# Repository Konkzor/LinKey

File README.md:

Moniteur **open-hardware** basse consommation à base d'ESP32 pour le compteur électrique **Linky** (monophasé), avec intégration native à **Home Assistant** via MQTT.

LinKey (jeu de mot) lit la sortie série TIC (Télé-Information Client) d'un Linky monophasé et publie les mesures de puissance, d'énergie et de courant vers le broker MQTT de votre Home Assistant. Le coprocesseur ULP de l'ESP32 décode la trame TIC pendant que le CPU principal reste en *light sleep*, ce qui maintient une consommation moyenne suffisamment faible pour fonctionner sur l'alimentation de la TIC via une supercapa.

## Fonctionnalités

- Décodage UART 7E1 (1200 bauds) par le coprocesseur ULP de l'ESP32
- Boucle principale en *light sleep* avec *modem sleep* WiFi
- Publication MQTT en QoS 1, *Last Will and Testament* et auto-découverte Home Assistant
- Alimentation par supercapa avec surveillance de tension intégrée
- Retour visuel par LED RGB
- Compatible contrats BASE, HP/HC, Tempo et EJP
- Mode TIC historique (standard à venir)

## Structure du dépôt

```
.
├── CAO/        Boîtier imprimable 3D (source STEP + modèle Onshape)
├── Doc/        Spécification TIC Linky et documents de référence
├── Firmware/   Projet ESP-IDF (ULP + machine d'état CPU, WiFi/MQTT)
└── PCB/        Projet KiCad, schéma, Gerbers

```

## Documentation

- [Guide du firmware](Firmware/README.md) — compilation, flashage, configuration, topics MQTT, découverte HA
- [Guide de la carte (PCB)](PCB/README.md) — composants, brochage ESP32, connexion TIC, fabrication
- [Guide du boîtier (CAO)](CAO/README.md) — source Onshape, STEP, paramètres d'impression
- [Spécification TIC Linky](Doc/Enedis-MOP-CPT_002E.pdf) — document de référence Enedis

## Firmware

Le firmware est un projet ESP-IDF situé dans [`Firmware/`](Firmware/). Consultez [`Firmware/README.md`](Firmware/README.md) pour le guide complet de compilation, flashage et configuration.

Démarrage rapide :

```bash
git clone --recurse-submodules https://github.com/Konkzor/LinKey.git
cd LinKey/Firmware
source ~/esp/v5.4.1/esp-idf/export.sh
idf.py menuconfig    # Configurer l'appareil et les options MQTT
idf.py -p /dev/ttyUSB0 flash monitor
```

Les identifiants WiFi sont provisionnés ensuite en BLE via l'application Espressif. Le firmware tente de découvrir Home Assistant en mDNS pour construire automatiquement l'URI MQTT (`mqtt://<ha-ip>:1883`), puis utilise `mqtt://homeassistant.local:1883` comme solution de repli.

L'identité MQTT par défaut est dérivée de l'adresse MAC WiFi : utilisateur `linkey_<suffixe_mac>` et topics `linkey/<suffixe_mac>/...`, par exemple `linkey/8ebde0/state`.

## PCB

Le PCB a été réalisé sous KiCad 9.

Les sources de la carte se trouvent dans [`PCB/`](PCB/). Voir [`PCB/README.md`](PCB/README.md) pour une description des composants, le brochage de l'ESP32 et la connexion TIC.

- Projet KiCad : [`PCB/LinKey.kicad_pro`](PCB/LinKey.kicad_pro)
- Modèles 3D de certains composants : [`PCB/MCAD files/`](PCB/MCAD%20files/)

> Note : Les fichiers de fabrication et la nomenclature ne sont pas versionnés dans le repo. Ils sont disponibles en artefacts des jobs de la CI ainsi que dans la [page Releases](https://github.com/Konkzor/LinKey/releases) pour les versions taguées.

## CAO

Le boîtier est conçu sous Onshape et imprimable en 3D.

Les sources se trouvent dans [`CAO/`](CAO/). Voir [`CAO/README.md`](CAO/README.md) pour le lien vers le modèle Onshape et les paramètres d'impression conseillés.

- Source CAO neutre (STEP) ;
- Fichiers prêts à imprimer (3MF multicolore, STL mono-couleur) : [page Releases](https://github.com/Konkzor/LinKey/releases).

## Licence

Ce projet utilise une **double licence** selon la nature des fichiers :

### Matériel — CERN-OHL-W-2.0

Le matériel (`PCB/` : sources KiCad, Gerbers… et `CAO/` : modèles 3D du boîtier, pièces mécaniques) est distribué sous **CERN Open Hardware Licence Version 2 – Weakly Reciprocal (CERN-OHL-W-2.0)**.

Vous êtes libre d'utiliser, d'étudier, de modifier et de fabriquer ce matériel.
Si vous modifiez les fichiers de conception eux-mêmes, vous devez publier ces modifications sous la même licence.
En revanche, vous n'êtes pas tenu de publier les sources de produits plus larges qui ne font qu'incorporer cette conception.

Texte complet : [`LICENSE`](LICENSE) (EN).

### Firmware — MIT

Le code du firmware (`Firmware/main/`) est distribué sous **licence MIT**, plus permissive et adaptée au logiciel.

Texte complet : [`Firmware/LICENSE`](Firmware/LICENSE) (EN).

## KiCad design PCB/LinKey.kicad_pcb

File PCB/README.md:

# LinKey — Carte électronique

Sources matérielles de la carte LinKey : projet KiCad, Gerbers et nomenclature.

> [!NOTE]
> La révision PCB est portée par les **tags git** `pcb-v*` (ex. `pcb-v1.0`). C'est la **source unique** : la CI dérive la version d'`git describe --tags --match 'pcb-v*'` et l'injecte à la fois dans le nom de l'artefact (`LinKey-pcb-<version>-fab`) et dans la variable de projet `PCB_VERSION` (Board Setup → Text Variables) pour que la sérigraphie `${PCB_VERSION}` reflète exactement l'état du dépôt :
>
> | Build | `${PCB_VERSION}` et nom d'artefact |
> |-------|------------------------------------|
> | Local (export manuel depuis KiCad) | `UNCONTROLLED` — valeur fixée en dur dans [`LinKey.kicad_pro`](LinKey.kicad_pro), signale que les fichiers de fab n'ont pas été produits par la CI et ne doivent pas être utilisés |
> | CI hors tag | `vX.Y-N-gSHA` (tag le plus récent + commits depuis + hash court) |
> | CI sur un tag `pcb-vX.Y` | `vX.Y` |

## Couche physique de la TIC Linky

> Source : [Enedis-NOI-CPT_54E](../Doc/Enedis-MOP-CPT_002E.pdf), §5.3.1 *Caractéristiques des signaux* (Table 3).

La sortie TIC du compteur Linky se présente sur le bornier client sous forme de **trois bornes** (`I1`, `I2`, `A`) : la paire `I1`/`I2` véhicule les **données**, et la paire `I1`/`A` est dédiée à l'**alimentation parasite** des récepteurs. Le compteur émet sur ce bus un **signal binaire modulé par tout-ou-rien sur une porteuse 50 kHz ± 3 %** (Table 3 de la spec Enedis), avec une **logique de codage négative** (porteuse présente ⇒ « 0 », porteuse absente ⇒ « 1 ») et une transmission **unidirectionnelle**.

> [!WARNING]
> Bien que les niveaux soient bas, le bus TIC reste relié au compteur — une **isolation galvanique côté récepteur reste obligatoire** pour la sécurité utilisateur et la conformité. C'est le rôle de l'optocoupleur (voir l'étage d'entrée ci-dessous).

Le bus est connecté à la carte via le connecteur **`J1`** (Samtec **HPM-03-04-T-S**, header 3 broches, pas 5 mm, sortie à angle droit).

## Architecture du PCB

L'architecture du PCB est composée de 2 branches principales :

```mermaid
flowchart LR
    TIC([TIC Linky J1<br/>I1, I2, A])

    TIC -->|I1 / A| D1[Pont redresseur<br/>D1]
    D1 --> Charge[Circuit de charge<br/>Q1, Q2, U4]
    Charge --> C2[(C2 — 1 F<br/>supercapa)]
    C2 --> Boost[Boost 3,3 V<br/>U5 — TPS61022]
    Boost --> ESP[ESP32 WROOM-32E<br/>+ périphériques]

    TIC -->|I1 / I2| U1[Opto AC/DC<br/>U1 — ACPL-214]
    U1 -->|RX — GPIO 14| ESP

    C2 -.->|ADC GPIO 33 — V_cap| ESP
```

- **Branche supérieure** : chemin d'alimentation, sur les bornes **`I1` / `A`** du Linky → pont redresseur → circuit de charge supercapa → `C2` → boost 3,3 V → ESP32.
- **Branche inférieure** : chemin de données, sur les bornes **`I1` / `I2`** du Linky → optocoupleur → ESP32.

Remarque : En **trait pointillé** la mesure de la tension du supercondensateur par l'ESP32.

### 1. Étage d'entrée

Sépare et conditionne les deux fonctions du bus TIC.

- **Démodulation des données** — `U1` (Broadcom **ACPL-214-500E**, opto **AC** SOP-4) extrait directement l'enveloppe de la porteuse 50 kHz et fournit un signal UART démodulé côté ESP32 (pull_up `R5` incluse), tout en assurant l'isolation galvanique.
- **Pont redresseur d'alimentation** — `D1` (Infineon **BAS 4002A RPP E6327**, array de Schottky basse Vf) forme un pont à quatre diodes dans un seul boîtier qui rectifie la porteuse 50 kHz pour alimenter le reste de la carte.

### 2. Circuit de charge du supercondensateur

Stocke l'énergie disponible pour absorber les pics de consommation pendant l'émission WiFi/MQTT. Limite le courant et la tension de charge.

- **Supercondensateur** — `C2` (KYOCERA AVX **SCCR12E105SRB**, 1 F / 3 V, ESR faible, radial 8×12 mm).
- Limitation de courant et tension contrôlant la tension Vgs de `Q2` (TI **CSD25402Q3A**, P-MOSFET 20 V) :
  - **Limitation de courant** — `Q1` (ON Semi **MMBT2907A**, PNP 60 V / 0,6 A) conjugué à `R10` (10 Ω) qui fixe le seuil de courant débité par l'étage d'entrée vers la supercapa à environ  40 mA.
  - **Limitation de tension** — `U4` (TI **TL431**, référence shunt ajustable) clampe la tension de charge à 2,7V de la supercapa (seuil réglé par `R15` et `R16`).

### 3. Alimentation 3,3 V (boost)

Convertit la tension variable du supercondensateur (0 V → 2,7 V) en un rail 3,3 V stable pour l'ESP32.

- **Convertisseur** — `U5` (TI **TPS61022**, boost synchrone 8 A pic, **démarrage à 1,5 V, maintien jusqu'à 0,5 V**) : on peut tirer du jus de la supercapa presque jusqu'à le vider complètement.
- **Inductance** — `L1` (Coilcraft **XEL5030-102MEC**, 1 µH), recommandée par TI.
- **Capacités** — `C3`, `C4` pour l'entrée, `C6` (22 µF / 10 V X7R 1206) pour la sortie.
- **Pont diviseur** — `R17` (453 k) / `R18` (100 k) pour régler la sortie à 3,3 V.

### 4. ESP32 et périphériques

- **MCU** — `U2` (Espressif **ESP32-WROOM-32E-N8**, 8 MB flash SPI, antenne PCB intégrée). Module choisi pour sa disponibilité du **coprocesseur ULP** que le firmware utilise pour décoder la TIC pendant le *light sleep*.
- **Découplage** — `C8` (100 nF), `C7` (22 µF).
- **Interface programmation/debug** — `J2` (header 4 broches, pas 2,54 mm) expose `TX`, `RX`, `GND`, `3V3` pour le flashage et le debug.
- **Boutons** — deux boutons tactiles Omron **B3U-1000P** :
  - `SW1` — **RESET**, raccordé sur la broche `EN` de l'ESP32 (tient le module en reset tant qu'il est pressé).
  - `SW2` — **BOOT**, raccordé sur `IO0` ; à maintenir pendant un reset pour entrer en mode flashage.
- **LED d'état RGB** — `D8` (American Bright **BL-HBXJXGX32L**, 5050 PLCC6) avec ses résistances de limitation `R6` (120 Ω) / `R8` (330 Ω) / `R9` (120 Ω) sur les trois canaux B/R/G respectivement. Pilotée par GPIO 2 / 13 / 15 ; flash bref de 10 ms à chaque itération de la FSM (voir `Firmware/README.md`).

## Affectation des broches (ESP32)

| Fonction | GPIO |
|----------|------|
| RX TIC Linky | 14 |
| ADC tension supercondensateur | 33 |
| LED RGB Rouge | 13 |
| LED RGB Verte | 15 |
| LED RGB Bleue | 2 |
| RX UART ESP | 3 |
| TX UART ESP | 1 |

## Contenu du dossier

| Fichier / dossier | Description |
|-------------------|-------------|
| [`LinKey.kicad_pro`](LinKey.kicad_pro) | Projet KiCad 9 |
| [`LinKey.kicad_sch`](LinKey.kicad_sch) | Schéma |
| [`LinKey.kicad_pcb`](LinKey.kicad_pcb) | Routage |
| [`fab-output.kicad_jobset`](fab-output.kicad_jobset) | Jobset KiCad décrivant les sorties de fabrication générées en CI |
| [`MCAD files/`](MCAD%20files/) | Modèles 3D des composants (STEP) |
| [`LinKey_Lib_Footprints.pretty/`](LinKey_Lib_Footprints.pretty/) | Bibliothèque d'empreintes du projet |
| [`LinKey_Lib_Symbols.kicad_sym`](LinKey_Lib_Symbols.kicad_sym) | Bibliothèque de symboles du projet |

## Fabrication

Les fichiers de fabrication ne sont **pas versionnés** : ils sont régénérés à chaque push par le workflow GitHub Actions [`.github/workflows/ci.yml`](../.github/workflows/ci.yml) (job `pcb-fab`) à partir du jobset [`fab-output.kicad_jobset`](fab-output.kicad_jobset), et publiés en tant qu'artefact nommé **`LinKey-pcb-<PCB_VERSION>-fab`** sur l'exécution correspondante (la version provient de la variable de projet `PCB_VERSION` — cf. note en haut de ce README).

Contenu de l'artefact :

| Fichier | Description |
|---------|-------------|
| `gerbers/LinKey-F_Cu.gbr`, `B_Cu.gbr`, `In1_Cu.gbr`, `In2_Cu.gbr` | Couches cuivre (4 couches) |
| `gerbers/LinKey-F_Mask.gbr`, `B_Mask.gbr` | Masques de soudure |
| `gerbers/LinKey-F_Paste.gbr`, `B_Paste.gbr` | Pochoir pâte à braser |
| `gerbers/LinKey-F_Silkscreen.gbr`, `B_Silkscreen.gbr` | Sérigraphies |
| `gerbers/LinKey-Edge_Cuts.gbr` | Contour de la carte |
| `gerbers/LinKey-job.gbrjob` | Métadonnées Gerber X2 (stackup) |
| `LinKey-PTH.drl`, `LinKey-NPTH.drl` | Perçages (plaqués / non plaqués) |
| `LinKey_positions-all.csv` | Fichier de positions (pick & place) |
| `LinKey_Bill_of_Materials.csv` | Nomenclature (BOM) |

Pour récupérer l'archive : ouvrir l'exécution CI sur GitHub → onglet *Summary* → section *Artifacts* → **`LinKey-pcb-<PCB_VERSION>-fab`**.

## Consommation

- ***Light sleep*** : à mesurer
- **Actif (publication)** : à mesurer
- **Moyenne** : à mesurer

## Licence

Voir le fichier [LICENSE](../LICENSE) à la racine du dépôt (CERN-OHL-W-2.0).

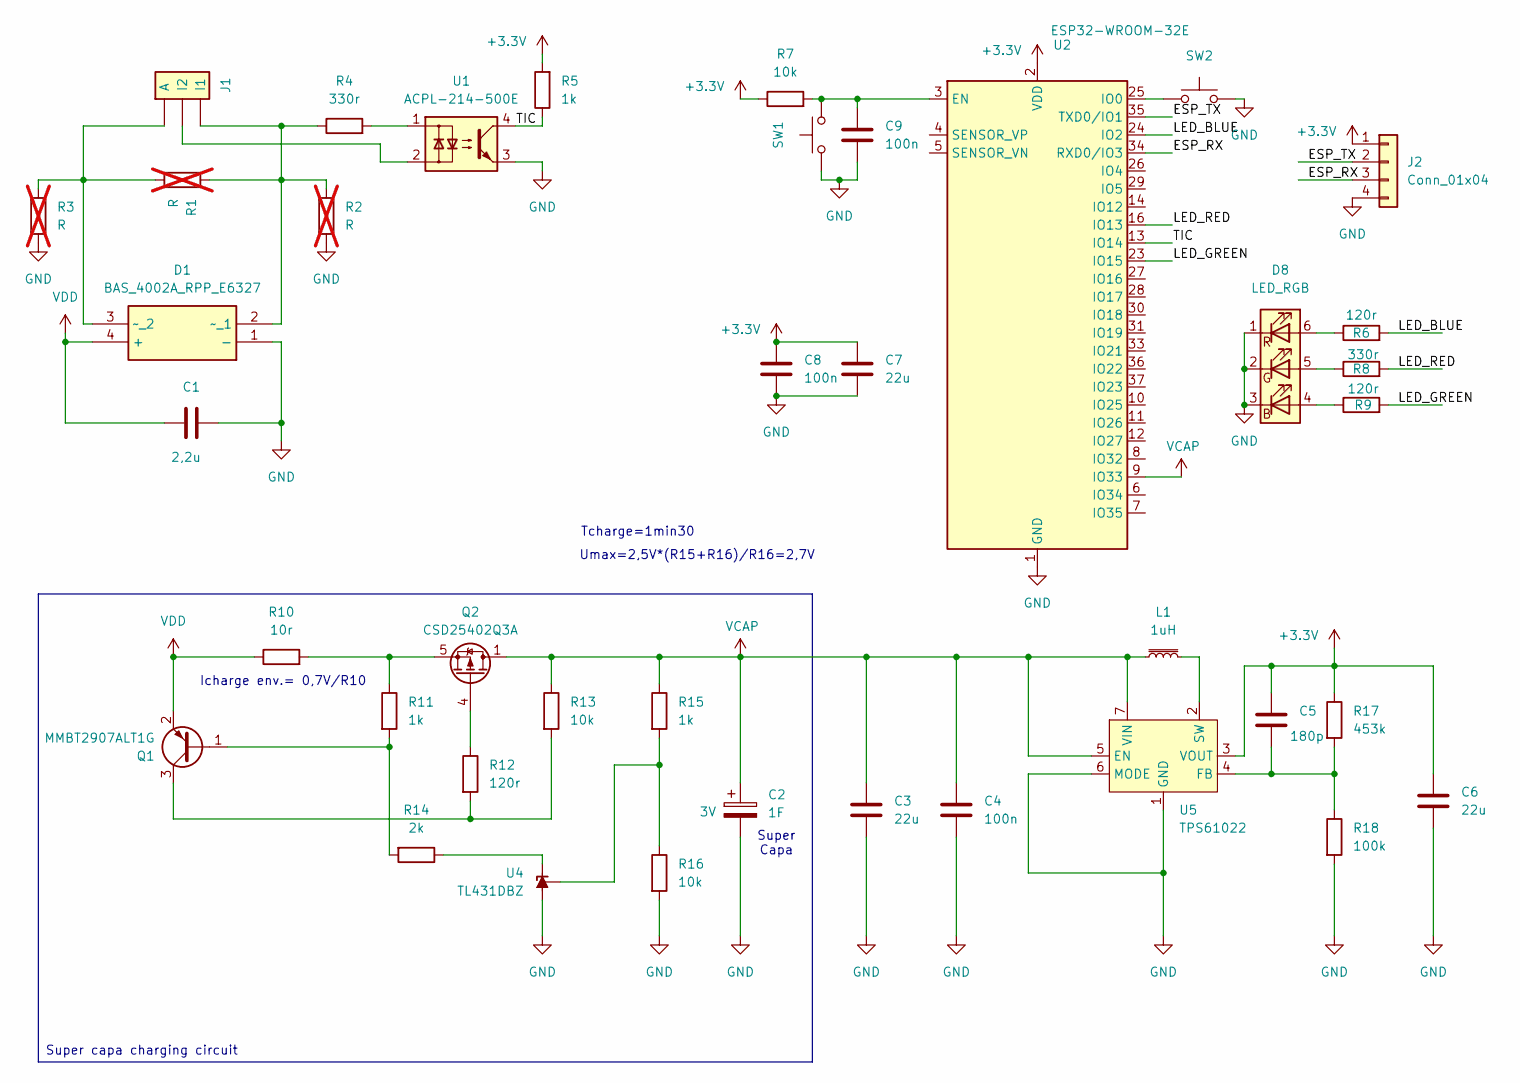
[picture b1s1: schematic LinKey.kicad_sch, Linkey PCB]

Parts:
C1: 2,2u; C_0805_2012Metric_Pad1.18x1.45mm_HandSolder; Voltage 16V; Manufacturer_Part_Number CL21B225KOFNNNF
C2: 1F; CP_Radial_D8.0mm_P3.50mm; Voltage 3V; Manufacturer_Part_Number SCCR12E105SRB
C3, C6, C7: 22u; C_1206_3216Metric_Pad1.33x1.80mm_HandSolder; Voltage 10V; Manufacturer_Part_Number CL31B226KPHNNNE
C4, C8, C9: 100n; C_0603_1608Metric_Pad1.08x0.95mm_HandSolder; Voltage 50V; Manufacturer_Part_Number CC0603JRX7R9BB104
C5: 180p; C_0603_1608Metric_Pad1.08x0.95mm_HandSolder; Voltage 50V; Manufacturer_Part_Number CC603KRX7R9BB181
D1: BAS_4002A_RPP_E6327; BAS4002ARPPE6327; Manufacturer_Part_Number BAS 4002A RPP E6327
D8: LED_RGB; LED_RGB_5050-6; Manufacturer_Part_Number BL-HBXJXGX32L
J1: Conn_01x03_TIC; Manufacturer_Part_Number HPM-03-04-T-S
J2: Conn_01x04; PinHeader_1x04_P2.54mm_Vertical
L1: 1uH; L_Coilcraft_XAL5030-XXX; Manufacturer_Part_Number XEL5030-102MEC
Q1: MMBT2907ALT1G; SOT-23_Handsoldering; Voltage 60V; Manufacturer_Part_Number MMBT2907ALT1G
Q2: CSD25402Q3A; VSON-8_3.3x3.3mm_P0.65mm_NexFET; Voltage 20V; Manufacturer_Part_Number CSD25402Q3A
R1, R2, R3: R; R_0603_1608Metric_Pad0.98x0.95mm_HandSolder; not fitted
R4, R8: 330r; R_0603_1608Metric_Pad0.98x0.95mm_HandSolder; Voltage 75V; Manufacturer_Part_Number CRCW0603330RFKEAC
R5, R11, R15: 1k; R_0603_1608Metric_Pad0.98x0.95mm_HandSolder; Voltage 75V; Manufacturer_Part_Number CRCW06031K00FKEAC
R6, R9, R12: 120r; R_0603_1608Metric_Pad0.98x0.95mm_HandSolder; Voltage 75V; Manufacturer_Part_Number CRCW0603120RFKEAC
R7, R13, R16: 10k; R_0603_1608Metric_Pad0.98x0.95mm_HandSolder; Voltage 75V; Manufacturer_Part_Number CRCW060310K0FKECC
R10: 10r; R_0805_2012Metric_Pad1.20x1.40mm_HandSolder; Voltage 150V; Manufacturer_Part_Number CRCW080510R0FKEA
R14: 2k; R_0603_1608Metric_Pad0.98x0.95mm_HandSolder; Voltage 75V; Manufacturer_Part_Number CRCW06032K00FKEAC
R17: 453k; R_0603_1608Metric_Pad0.98x0.95mm_HandSolder; Manufacturer_Part_Number CRCW0603453KFKEAC
R18: 100k; R_0603_1608Metric_Pad0.98x0.95mm_HandSolder; Voltage 75V; Manufacturer_Part_Number CRCW0603100KFKEAC
SW1, SW2: B3U-1000P; Manufacturer_Part_Number B3U-1000P
U1: ACPL-214-500E; SOP-4_4.4x2.6mm_P1.27mm; Manufacturer_Part_Number ACPL-214-500E
U2: ESP32-WROOM-32E; Manufacturer_Part_Number ESP32-WROOM-32E-N8
U4: TL431DBZ; SOT-23; Manufacturer_Part_Number TL431AIDBZR
U5: TPS61022; Texas_RWU0007A_VQFN-7_2x2mm_P0.5mm; Manufacturer_Part_Number TPS61022RWUT

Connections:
+3.3V: C5.1, C6.1, C7.1, C8.1, J2.1, R5.2, R7.1, R17.1, U2.2 (VDD), U5.3 (VOUT)
/ESP_RX: J2.3, U2.34 (RXD0/IO3)
/ESP_TX: J2.2, U2.35 (TXD0/IO1)
/LED_BLUE: R6.2, U2.24 (IO2)
/LED_GREEN: R9.2, U2.23 (IO15)
/LED_RED: R8.2, U2.16 (IO13)
/TIC: R5.1, U1.4, U2.13 (IO14)
GND: C1.2, C2.2, C3.2, C4.2, C6.2, C7.2, C8.2, C9.2, D1.1 (-), D8.1 (RK), D8.2 (GK), D8.3 (BK), J2.4, R2.2, R3.2, R16.2, R18.2, SW1.1, SW2.2, U1.3, U2.1 (GND), U2.15 (GND), U2.38 (GND), U2.39 (GND), U4.3 (A), U5.1 (GND), U5.6 (MODE)
unnamed: D1.2 (~_1), J1.3 (I1), R1.1, R2.1, R4.1
unnamed: D1.3 (~_2), J1.1 (A), R1.2, R3.1
unnamed: D8.4 (BA), R9.1
unnamed: D8.5 (GA), R8.1
unnamed: D8.6 (RA), R6.1
unnamed: J1.2 (I2), U1.2
unnamed: Q1.1 (B), R11.2, R14.2
unnamed: Q1.3 (C), R12.2, R13.2
unnamed: Q2.4 (G), R12.1
unnamed: Q2.5 (S), R10.2, R11.1
unnamed: R4.2, U1.1
unnamed: C9.1, R7.2, SW1.2, U2.3 (EN)
unnamed: SW2.1, U2.25 (IO0)
unnamed: R14.1, U4.1 (K)
unnamed: R15.2, R16.1, U4.2 (REF)
unnamed: C5.2, R17.2, R18.1, U5.4 (FB)
unnamed: L1.2, U5.2 (SW)
VCAP: C2.1, C3.1, C4.1, L1.1, Q2.1 (D), Q2.2 (D), Q2.3 (D), R13.1, R15.1, U2.9 (IO33), U5.5 (EN), U5.7 (VIN)
VDD: C1.1, D1.4 (+), Q1.2 (E), R10.1

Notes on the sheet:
Icharge env.= 0,7V/R10
Tcharge=1min30
Super Capa
Umax=2,5V*(R15+R16)/R16=2,7V
Super capa charging circuit

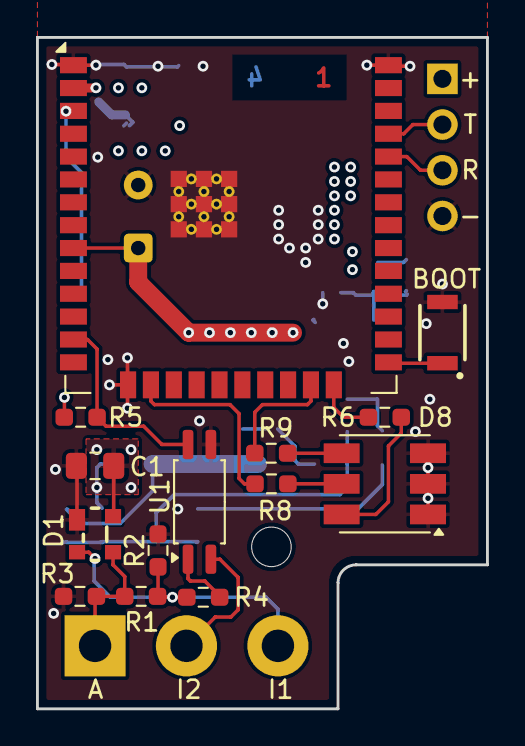
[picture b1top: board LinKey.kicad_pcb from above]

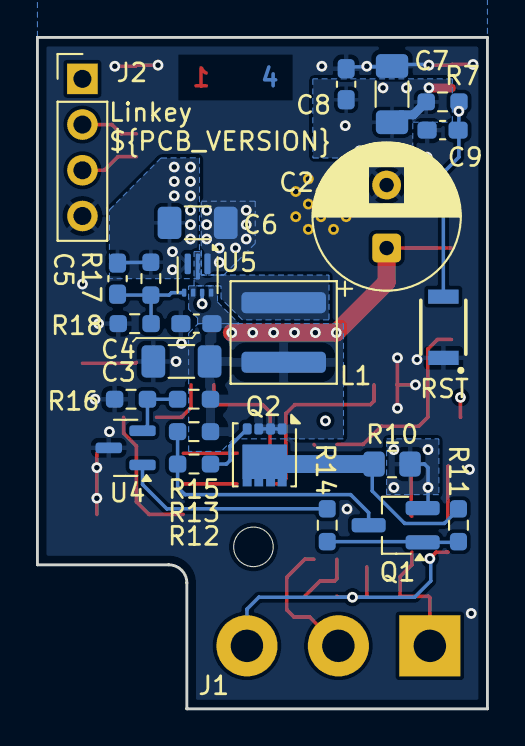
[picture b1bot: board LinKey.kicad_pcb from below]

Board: 4 copper layers, 25.0 x 37.3 mm, 40 parts (26 on the bottom side), 27 nets.

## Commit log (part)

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2025-10-26 Commit initial ESP32 firmware
2025-10-27 Remove duplicated codes
2025-10-27 Fix immediate wakeup from light sleep
2025-11-27 Improve LIGHT SLEEP mode to wake up every 1s, keeping wifi connected and send mqtt messages
2026-01-26 Fix Linky RX GPIO configuration to use GPIO_NUM_14
2026-01-26 Add RGB LED and supercap ADC initialization functions
2026-02-07 Refactor main application with FSM architecture and modular managers
    Architecture:
    - Finite State Machine (FSM) with 6 states: INIT, WAIT_VOLTAGE, WIFI_CONNECT, MQTT_CONNECT, WAIT_ULP_DATA, PUBLISH_DATA
    - Dependency injection pattern: wifi_state_t and mqtt_state_t structs owned by main, passed to manager modules
    - Shared types in types.h: conn_result_t enum (CONN_OK, CONN_FAILED, CONN_VOLTAGE_LOW) and voltage_check_fn_t callback
    - Modular design: wifi_manager and mqtt_manager handle their respective subsystems independently
    Power Management:
2026-02-07 Ignore .cache folder
2026-02-08 Add Home Assistant MQTT auto-discovery support
    - Single JSON state topic (<prefix>/state) instead of separate topics
    - LWT for availability (<prefix>/status with online/offline)
    - Auto-publish HA discovery configs on MQTT connect
    - Device grouped by MAC address (linkey_<mac>)
    - Sensors: Current (A), Energy Index (Wh), Supercap Voltage (mV)
2026-02-08 refactor: rename Kconfig entries from LINKY to LINKEY
    Standardize naming across all configuration options and add
    CONFIG_LINKEY_DEVICE_NAME for configurable HA device name.
2026-02-08 feat: add uptime sensor and improve HA discovery
    - Add uptime_s field to linky_data_t
    - Add state_class for proper HA statistics (total_increasing for energy/uptime, measurement for current/voltage)
    - Add custom MDI icons for all sensors
2026-02-11 feat: add PAPP and ADPS sensors, use HA abbreviated keys
    Add apparent power (PAPP) and overcurrent warning (ADPS) sensors.
    Fix debug logs to print parsed values instead of uninitialized data.
    Use HA abbreviated discovery keys to reduce payload size.
2026-02-11 docs: update README and replace TIC specification document
    Update README with HA integration, FSM architecture, new sensors
    (PAPP, ADPS, uptime), MQTT JSON topics, and project structure.
    Replace Enedis-NOI-CPT_54E with Enedis-MOP-CPT_002E specification.
2026-02-16 refactor: extract voltage management into dedicated module
    Move ADC init, voltage reading, fixed/dynamic threshold checks and
    peak tracking from main.c into voltage_manager.c/h.
2026-02-18 fix: remove emergency WiFi stop from MQTT event handler
    Let the normal FSM handle connection recovery on MQTT message expiry
    instead of killing WiFi from within the event handler.
2026-02-24 refactor: define TIC protocol bytes as LINKY_TIC_ macros
    Replace hardcoded 0x02/0x03/'\n'/'\r' with named macros and use
    LINKY_TIC_GROUP_SEP instead of isspace() for field separator matching.
    - LINKY_TIC_FRAME_START (0x02), LINKY_TIC_FRAME_END (0x03)
    - LINKY_TIC_GROUP_START (0x0A), LINKY_TIC_GROUP_END (0x0D)
    - LINKY_TIC_GROUP_SEP (0x09)
2026-02-24 refactor: replace line buffers with double-buffered frame reception
    Replace 10-16 separate line buffers (LF-terminated) with two ping-pong
    frame buffers using ETX (0x03) as UART RX termination character. Each
    reception now captures a complete TIC frame set, eliminating per-tariff
    buffer count conditionals and race conditions between ULP and CPU.
    - ULP alternates writing between buf_0 and buf_1, signaling CPU via
    ulp_active_buf which buffer to read (always the completed one)
2026-02-24 fix: only publish energy indexes on value change
2026-02-24 feat: use ULP wake ISR instead of fixed 1s polling
    Register a ULP interrupt handler that notifies the main task via
    FreeRTOS task notification when I_WAKE() fires. The CPU now sleeps
    until the ULP signals a new frame is ready, instead of polling
    every second.
    - Add ulp_isr() with vTaskNotifyGiveFromISR on ULP wake
    - ulp_wait_data() blocks on ulTaskNotifyTake instead of vTaskDelay
2026-02-24 fix: don't disconnect on MQTT outbox message expiry
    MQTT_EVENT_DELETED only means a QoS message expired from the outbox,
    not that the connection is lost. MQTT_EVENT_DISCONNECTED handles that.
2026-02-24 refactor: table-driven TIC label parsing in process_message
    Replace repetitive str_starts_with/parse chains with a linky_labels[]
    descriptor table. Each entry defines: label string, expected data
    length, unit, valid flag, struct offset and field size.
    - FIELD() macro derives offset and size from the struct member
    - Single loop matches labels and stores values generically
    - Eliminates ~90 lines of duplicated parsing code
2026-04-26 Fix model path for Conn_01x03 footprint in KiCad library
2026-04-26 Update R11 position and J1's 3D model
    - Slightly move R11 away from the PCB edge
    - Add J1's 3D model
    - Complete J1's BOM data = Samtech vertical header that must be manually bent
2026-04-26 Release PCB v1
2026-04-26 Add BAS_4002A symbol into local lib
2026-04-26 Output fab files (Gerber, NC Drill and BOM)
2026-04-26 Update pcb version to v1.1
    - Fix R10 footprint (was 1206 but should be 0805), decrease value to increase max current to 40mA
    - Change R15/R16 values (divided by 10)
    - Increase R11 from 200r to 1k to fix voltage limitation
    - Fix I1/I2 swap
    - Modify R4, R5 values around opto
    - Add SW + Capa on EN
2026-04-28 Remove obsolete Gerber and MCAD design files
2026-04-28 docs: add project READMEs and licensing
    - Add root README with project overview, repo structure, PCB image and dual-licensing summary
    - Add LICENSE at root (CERN-OHL-W-2.0) covering hardware (PCB and future CAO files)
    - Add Firmware/LICENSE (MIT) and rewrite Firmware/README.md:
    - System overview with CPU/ULP split diagram
    - FSM section with Mermaid composite-state diagram and per-state LED colors
    - Accurate TIC frame description (frame = STX + dataset(s) + ETX) sourced from Enedis spec
2026-04-29 docs: add new images and README for LinKey PCB project
2026-04-29 Update PCB v1.1 to better pass DRC
2026-05-15 docs: add banner on top of main README.md
2026-05-15 fix: track sdkconfig.defaults so CI gets ULP/PM config
2026-05-15 refactor: extract tic_parser from ulp_linky
    Move the pure-C TIC parsing (checksum, group parsing, label dispatch)
    out of ulp_linky.cpp into a new host-testable tic_parser module,
    mirroring the voltage_state pattern. Shared types move into
    tic_types.h; ulp_linky.cpp keeps the ULP/RTC layer only.
    Bundled fix: debug.h includes esp_log.h only when debug logs are
    enabled, so logic files compile on host with no stubs.
2026-05-15 refactor: extract voltage_state from voltage_manager
    Move the threshold + dynamic-peak math out of voltage_manager.c into a
    pure voltage_state.{c,h} pair with no ESP-IDF dependencies. The peak
    tracker is now a caller-owned voltage_state_t rather than a file-static,
    following the wifi_state_t / mqtt_state_t convention.
    voltage_manager.c remains the ADC shim: owns a single voltage_state_t
    and forwards voltage_is_low / voltage_is_low_dynamic / voltage_reset_peak
2026-05-15 test: add host unit tests for voltage_state and CI workflow
    Set up a standalone CMake project under Firmware/test/host/ that pulls
    Unity v2.6.0 via FetchContent and builds host-side unit tests against
    the pure-logic modules. 13 cases cover voltage_state_is_low,
    voltage_state_is_low_dynamic (peak tracking, drop tolerance, floor
    clamp) and voltage_state_reset_peak.
    GitHub Actions workflow runs two jobs on every push and PR:
2026-05-16 ci: add KiCad DRC and fab file generation jobs
    Drop the committed Gerber/drill outputs since CI now produces them as
    artifacts from the source .kicad_pcb on every push.
2026-05-16 ci: add initial DRC rules for Q2 pad clearance to fix CI
2026-05-16 ci: drive fab generation from kicad jobset
    Use kicad-cli jobset so layer/output selection lives in the project
    instead of being duplicated in YAML. Document the resulting CI artifact
    contents in PCB/README.md, ignore the generated fab-output/ folder, and
    drop the manually exported BOM CSV (now produced by CI).
2026-05-17 refactor(pcb): derive PCB version from git tag pcb-v*
    - CI computes version via 'git describe --tags --match pcb-v*' and
    injects it into text_variables.PCB_VERSION in LinKey.kicad_pro before
    running the jobset, so silkscreen ${PCB_VERSION} reflects the build
    - fetch-depth: 0 on checkout so describe sees tags
    - Artifact name LinKey-pcb-<version>-fab (e.g. v1.0, or v1.0-N-gSHA off-tag)
    - Local kicad_pro pins PCB_VERSION to UNCONTROLLED to flag manual exports
2026-05-17 ci: fetch tags and bypass safe.directory for git describe in container
    - fetch-tags: true on checkout (fetch-depth: 0 alone doesn't always pull
    tags when actions/checkout runs inside a container)
    - Mark workspace as safe.directory before git describe, to avoid the
    dubious-ownership refusal that surfaces in container contexts
    - Drop the 2>/dev/null mask so the real git error is visible if describe
    still fails for any reason
2026-05-17 ci: trigger on pcb-v* and release tags
    Listen for tag pushes matching pcb-v* (PCB revision tags) and the
    YY.N release scheme (e.g. 26.1) so fab artifacts produced on a tagged
    commit get the clean version name without the -N-gSHA suffix.
2026-05-17 chore: ignore qemu.log from local boot-smoke runs
2026-05-17 ci: build firmware inside boot-smoke job to avoid idf.py qemu rebuild
    idf.py qemu always invokes the build target as a dependency. When the
    boot-smoke job downloaded the firmware-build artifact, ninja saw the
    restored mtimes as newer than sources and triggered a full re-build that
    exceeded the 20s QEMU timeout, so QEMU never started and app_main was
    never reached.
    Move the build into the boot-smoke job itself. With a warm build in the
2026-05-17 test: extend host test edge cases for tic_parser and voltage_state
    tic_parser (+5):
    - null group pointer safety mirror of existing null-data test
    - value shorter than expected (consumed-length mismatch)
    - non-digit byte in value rejected by parse_uint length check
    - extra separators between label and value tolerated
    - null frame pointer safety
2026-05-17 refactor(fsm): extract pure FSM transition logic into main/fsm.{h,c}
    Each handle_state_* handler keeps its IDF/side-effect calls; the post-call
    switch on conn_result_t (and the per-iteration watchdog + peak-reset rules
    in app_main) move to fsm.{h,c} as pure functions. app_state_t moves to
    fsm.h so tests can use it. Handler behavior, call ordering and log lines
    are preserved.
    test: add test_main_fsm covering all 6 pure functions
2026-05-19 test: add comprehensive tests for BASE, HPHC, EJP, and TEMPO frames in tic_parser
    - Frames are supposed to be representative of real-world data
    for BASE, HPHC and TEMPO.
    - EJP test omplete frame has not been verified.
    - Added tests needed to include all LABEL, VALID_FLAG and linky_data_t
    and linky_label_t content unconditionnally (Duplicated flag values are mutually exclusive).
2026-05-27 Add QEMU firmware emulation target
    - add QEMU emulation component with hardware wrappers for ULP, voltage, WiFi, and power
    management
    - add deterministic TIC test frames for BASE, HPHC, EJP, and TEMPO tariffs
    - add run_qemu_linkey.sh with --tariff_option support and tariff-specific build dirs
    - add QEMU sdkconfig defaults and local Mosquitto broker config
    - document QEMU build, launch, MQTT broker, and validation workflow
2026-05-27 docs: update EMULATION.md with detailed emulation coverage status
2026-05-31 ci: validate QEMU MQTT emulation
    Replace the QEMU boot smoke test with tariff-based MQTT emulation checks.
    - Run QEMU CI across base, hphc, ejp, and tempo tariffs
    - Start a local Mosquitto broker and capture MQTT traffic
    - Validate online status, Home Assistant discovery, and state topics
    - Add MQTT assertion helper for tariff-specific discovery components
    - Use deterministic QEMU WiFi STA MAC AA:BB:CC:DD:EE:FF
2026-05-31 chore: remove release version header and tag explanation from release template
2026-05-31 docs: clarify that the firmware is for a monophasé Linky meter

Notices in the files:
PCB/README.md:
Voir le fichier [LICENSE](../LICENSE) à la racine du dépôt (CERN-OHL-W-2.0).
README.md:
Hardware License: CERN-OHL-W-2.0
